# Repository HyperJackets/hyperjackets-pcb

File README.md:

# PCB Designs

The PCBs are designed as shields that fit a Nucleo-144 development board. CAN (DB9) is used for interboard communication. Boards are powered at 10v by the JST connector unless otherwise specified.

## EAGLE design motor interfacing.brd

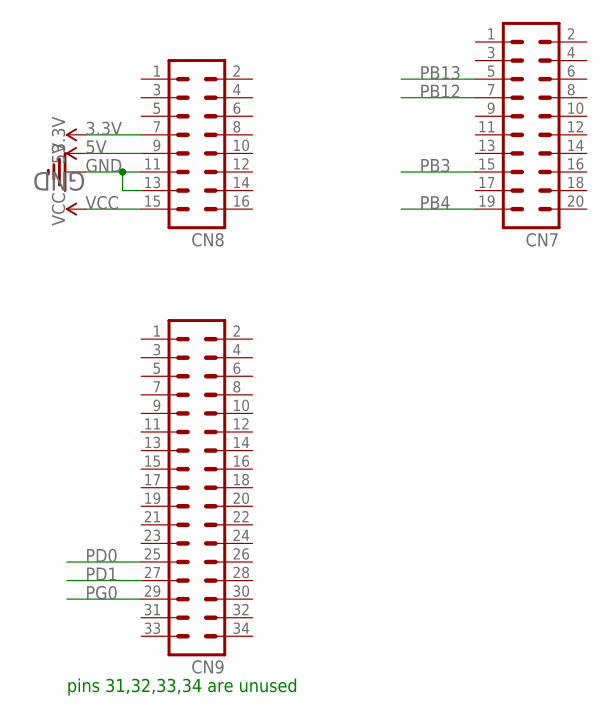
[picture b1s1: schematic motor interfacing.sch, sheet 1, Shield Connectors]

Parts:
CN7: MA10-2
CN8: MA08-2
CN9: MA17-2

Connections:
3.3V: CN8.7
5V: CN8.9; also elsewhere on the board
GND: CN8.11, CN8.13; also elsewhere on the board
PB3: CN7.15; also elsewhere on the board
PB4: CN7.19; also elsewhere on the board
PB12: CN7.7; also elsewhere on the board
PB13: CN7.5; also elsewhere on the board
PD0: CN9.25; also elsewhere on the board
PD1: CN9.27; also elsewhere on the board
PG0: CN9.29; also elsewhere on the board
VCC: CN8.15; also elsewhere on the board

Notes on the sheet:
pins 31,32,33,34 are unused

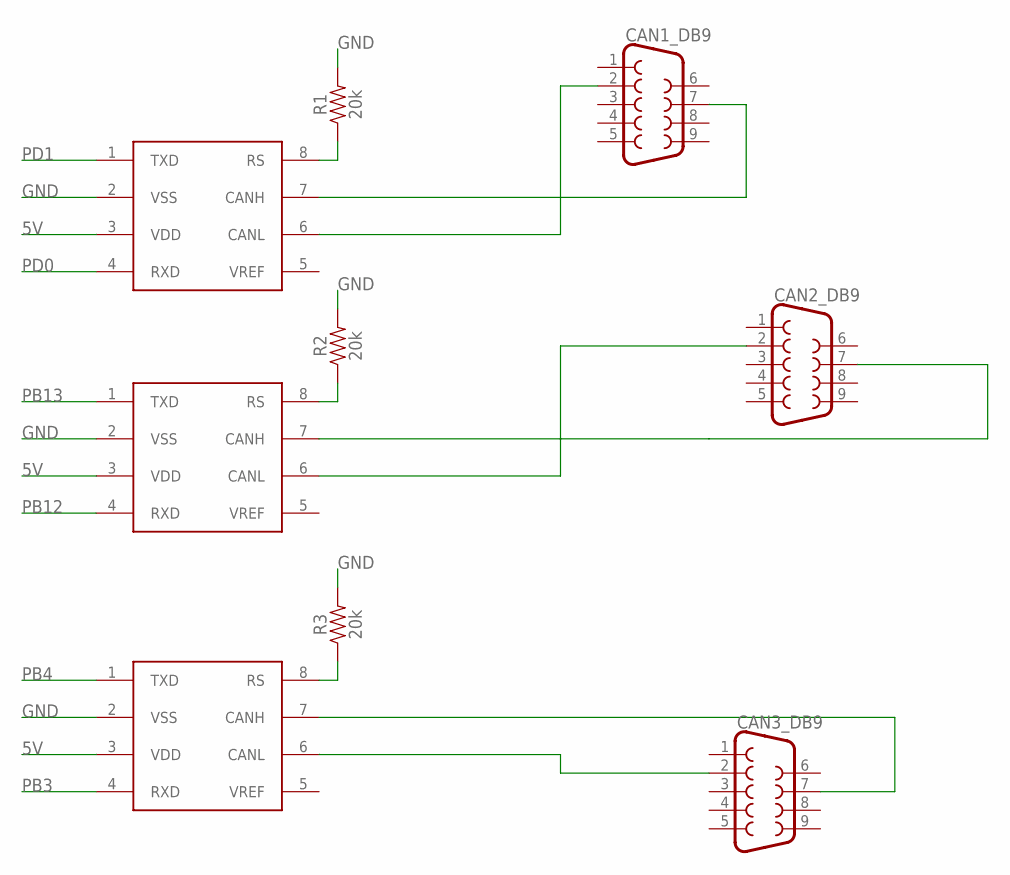
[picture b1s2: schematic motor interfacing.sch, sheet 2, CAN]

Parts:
CAN1, CAN2, CAN3: MCP2551; MPC2551
CAN1_DB9, CAN2_DB9, CAN3_DB9: DB9FEMALE; DB9
R1, R2, R3: 20k; AXIAL-0.3

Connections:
5V: CAN1.3 (VDD), CAN2.3 (VDD), CAN3.3 (VDD); also elsewhere on the board
GND: CAN1.2 (VSS), CAN2.2 (VSS), CAN3.2 (VSS), R1.P$2 (2), R2.P$2 (2), R3.P$2 (2); also elsewhere on the board
unnamed: CAN1.7 (CANH), CAN1_DB9.7
unnamed: CAN1.6 (CANL), CAN1_DB9.2
unnamed: CAN2.6 (CANL), CAN2_DB9.2
unnamed: CAN3.6 (CANL), CAN3_DB9.2
unnamed: CAN3.7 (CANH), CAN3_DB9.7
unnamed: CAN1.8 (RS), R1.P$1 (1)
unnamed: CAN2.8 (RS), R2.P$1 (1)
unnamed: CAN3.8 (RS), R3.P$1 (1)
unnamed: CAN2.7 (CANH), CAN2_DB9.7
PB3: CAN3.4 (RXD); also elsewhere on the board
PB4: CAN3.1 (TXD); also elsewhere on the board
PB12: CAN2.4 (RXD); also elsewhere on the board
PB13: CAN2.1 (TXD); also elsewhere on the board
PD0: CAN1.4 (RXD); also elsewhere on the board
PD1: CAN1.1 (TXD); also elsewhere on the board

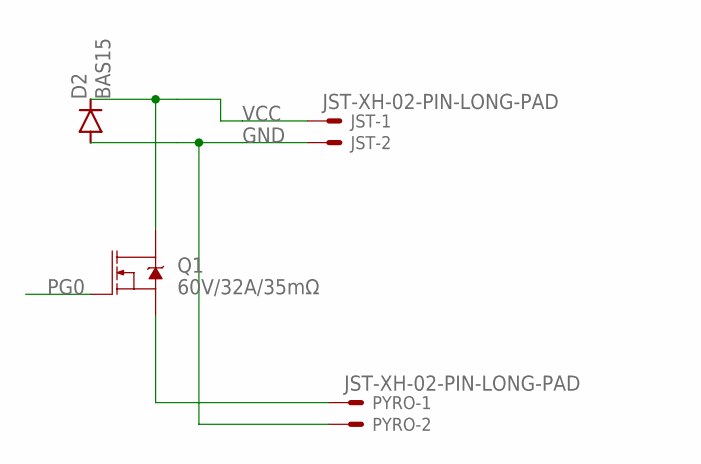
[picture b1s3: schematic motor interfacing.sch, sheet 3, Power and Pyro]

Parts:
D2: BAS15; DO34-7
JST: JST-XH-02-PIN-LONG-PAD; JST-XH-02-PACKAGE-LONG-PAD
PYRO: JST-XH-02-PIN-LONG-PAD; JST-XH-02-PACKAGE-LONG-PAD
Q1: 60V/32A/35mΩ; TO220V

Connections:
GND: D2.A, JST.2, PYRO.2; also elsewhere on the board
unnamed: PYRO.1, Q1.3 (S)
PG0: Q1.1 (G); also elsewhere on the board
VCC: D2.C, JST.1, Q1.2 (D); also elsewhere on the board

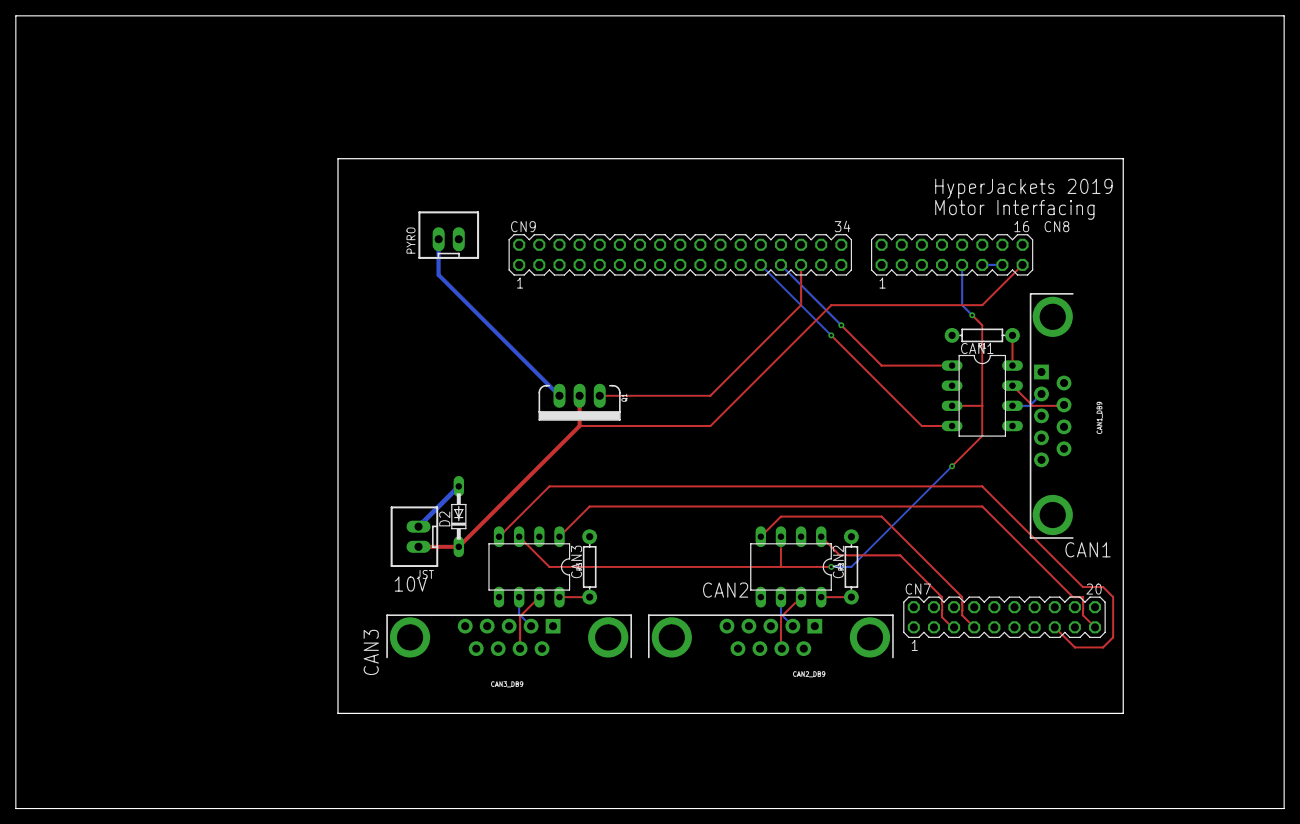
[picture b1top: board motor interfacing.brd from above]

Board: 2 copper layers, 160.0 x 100.0 mm, 16 parts (0 on the bottom side), 20 nets.

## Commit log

2019-04-05 add motor interfacing board and gitignore
2019-04-05 Add basic info to README
2019-04-11 Update motor interfacing board

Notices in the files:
parts and their libraries:
SparkFun-Connectors: Licensing: Creative Commons ShareAlike 4.0 International - https://creativecommons.org/licenses/by-sa/4.0
